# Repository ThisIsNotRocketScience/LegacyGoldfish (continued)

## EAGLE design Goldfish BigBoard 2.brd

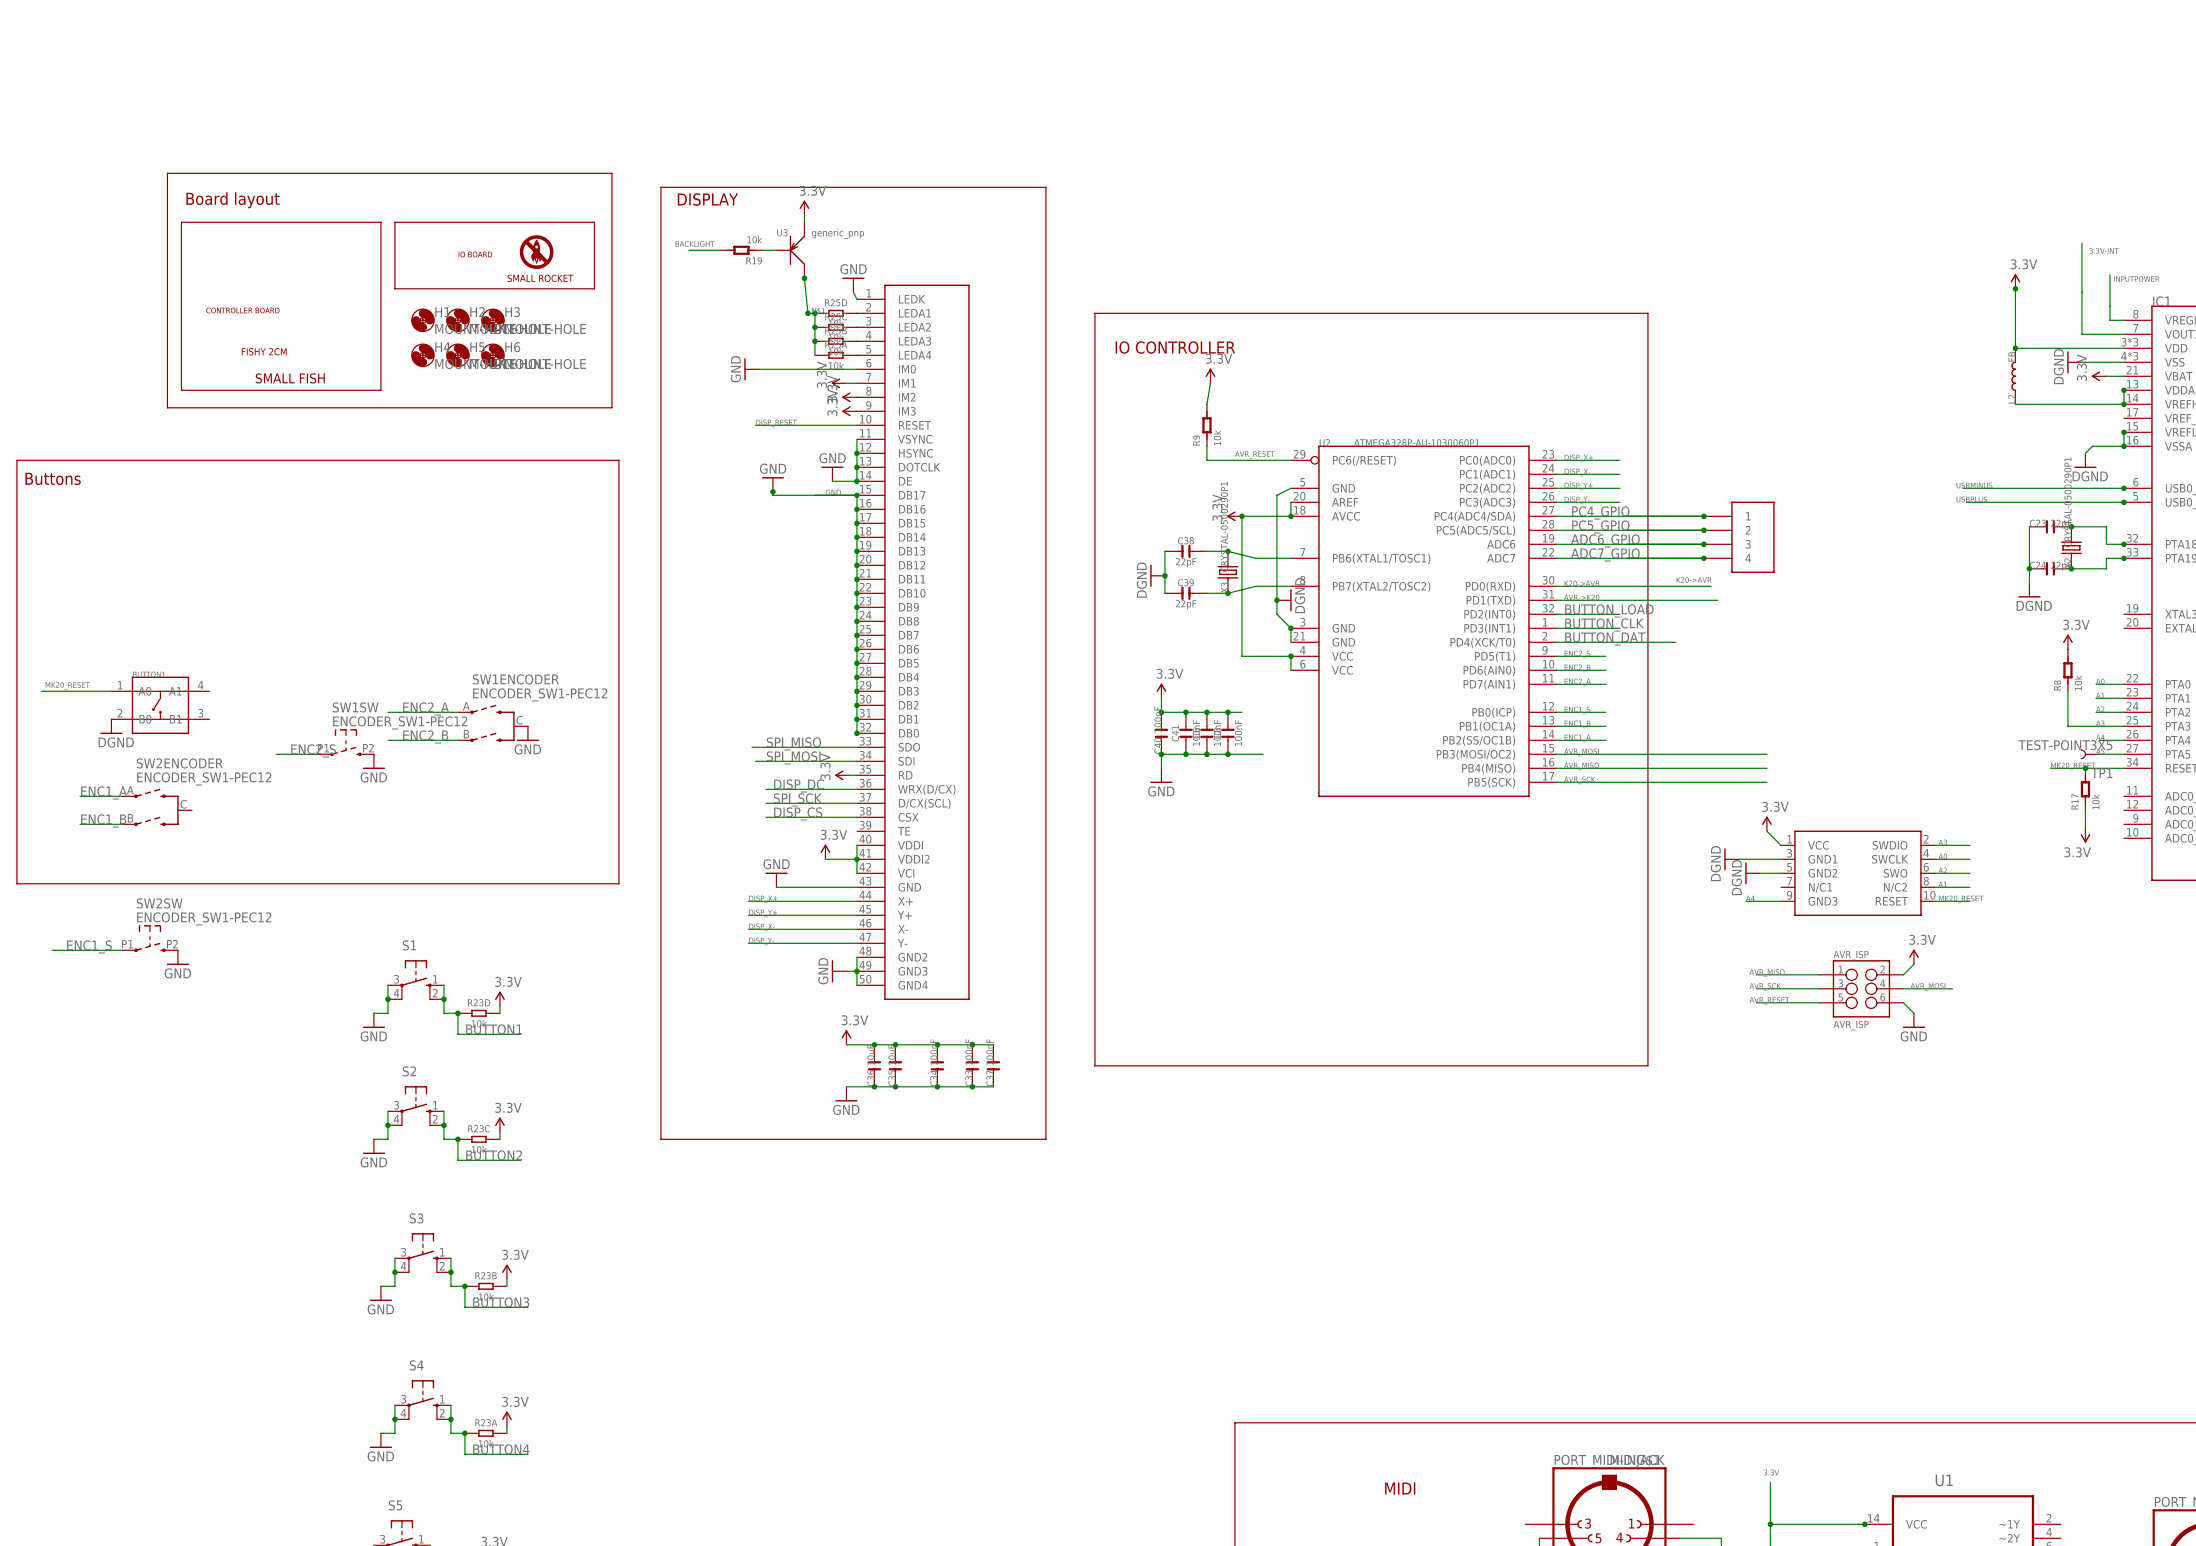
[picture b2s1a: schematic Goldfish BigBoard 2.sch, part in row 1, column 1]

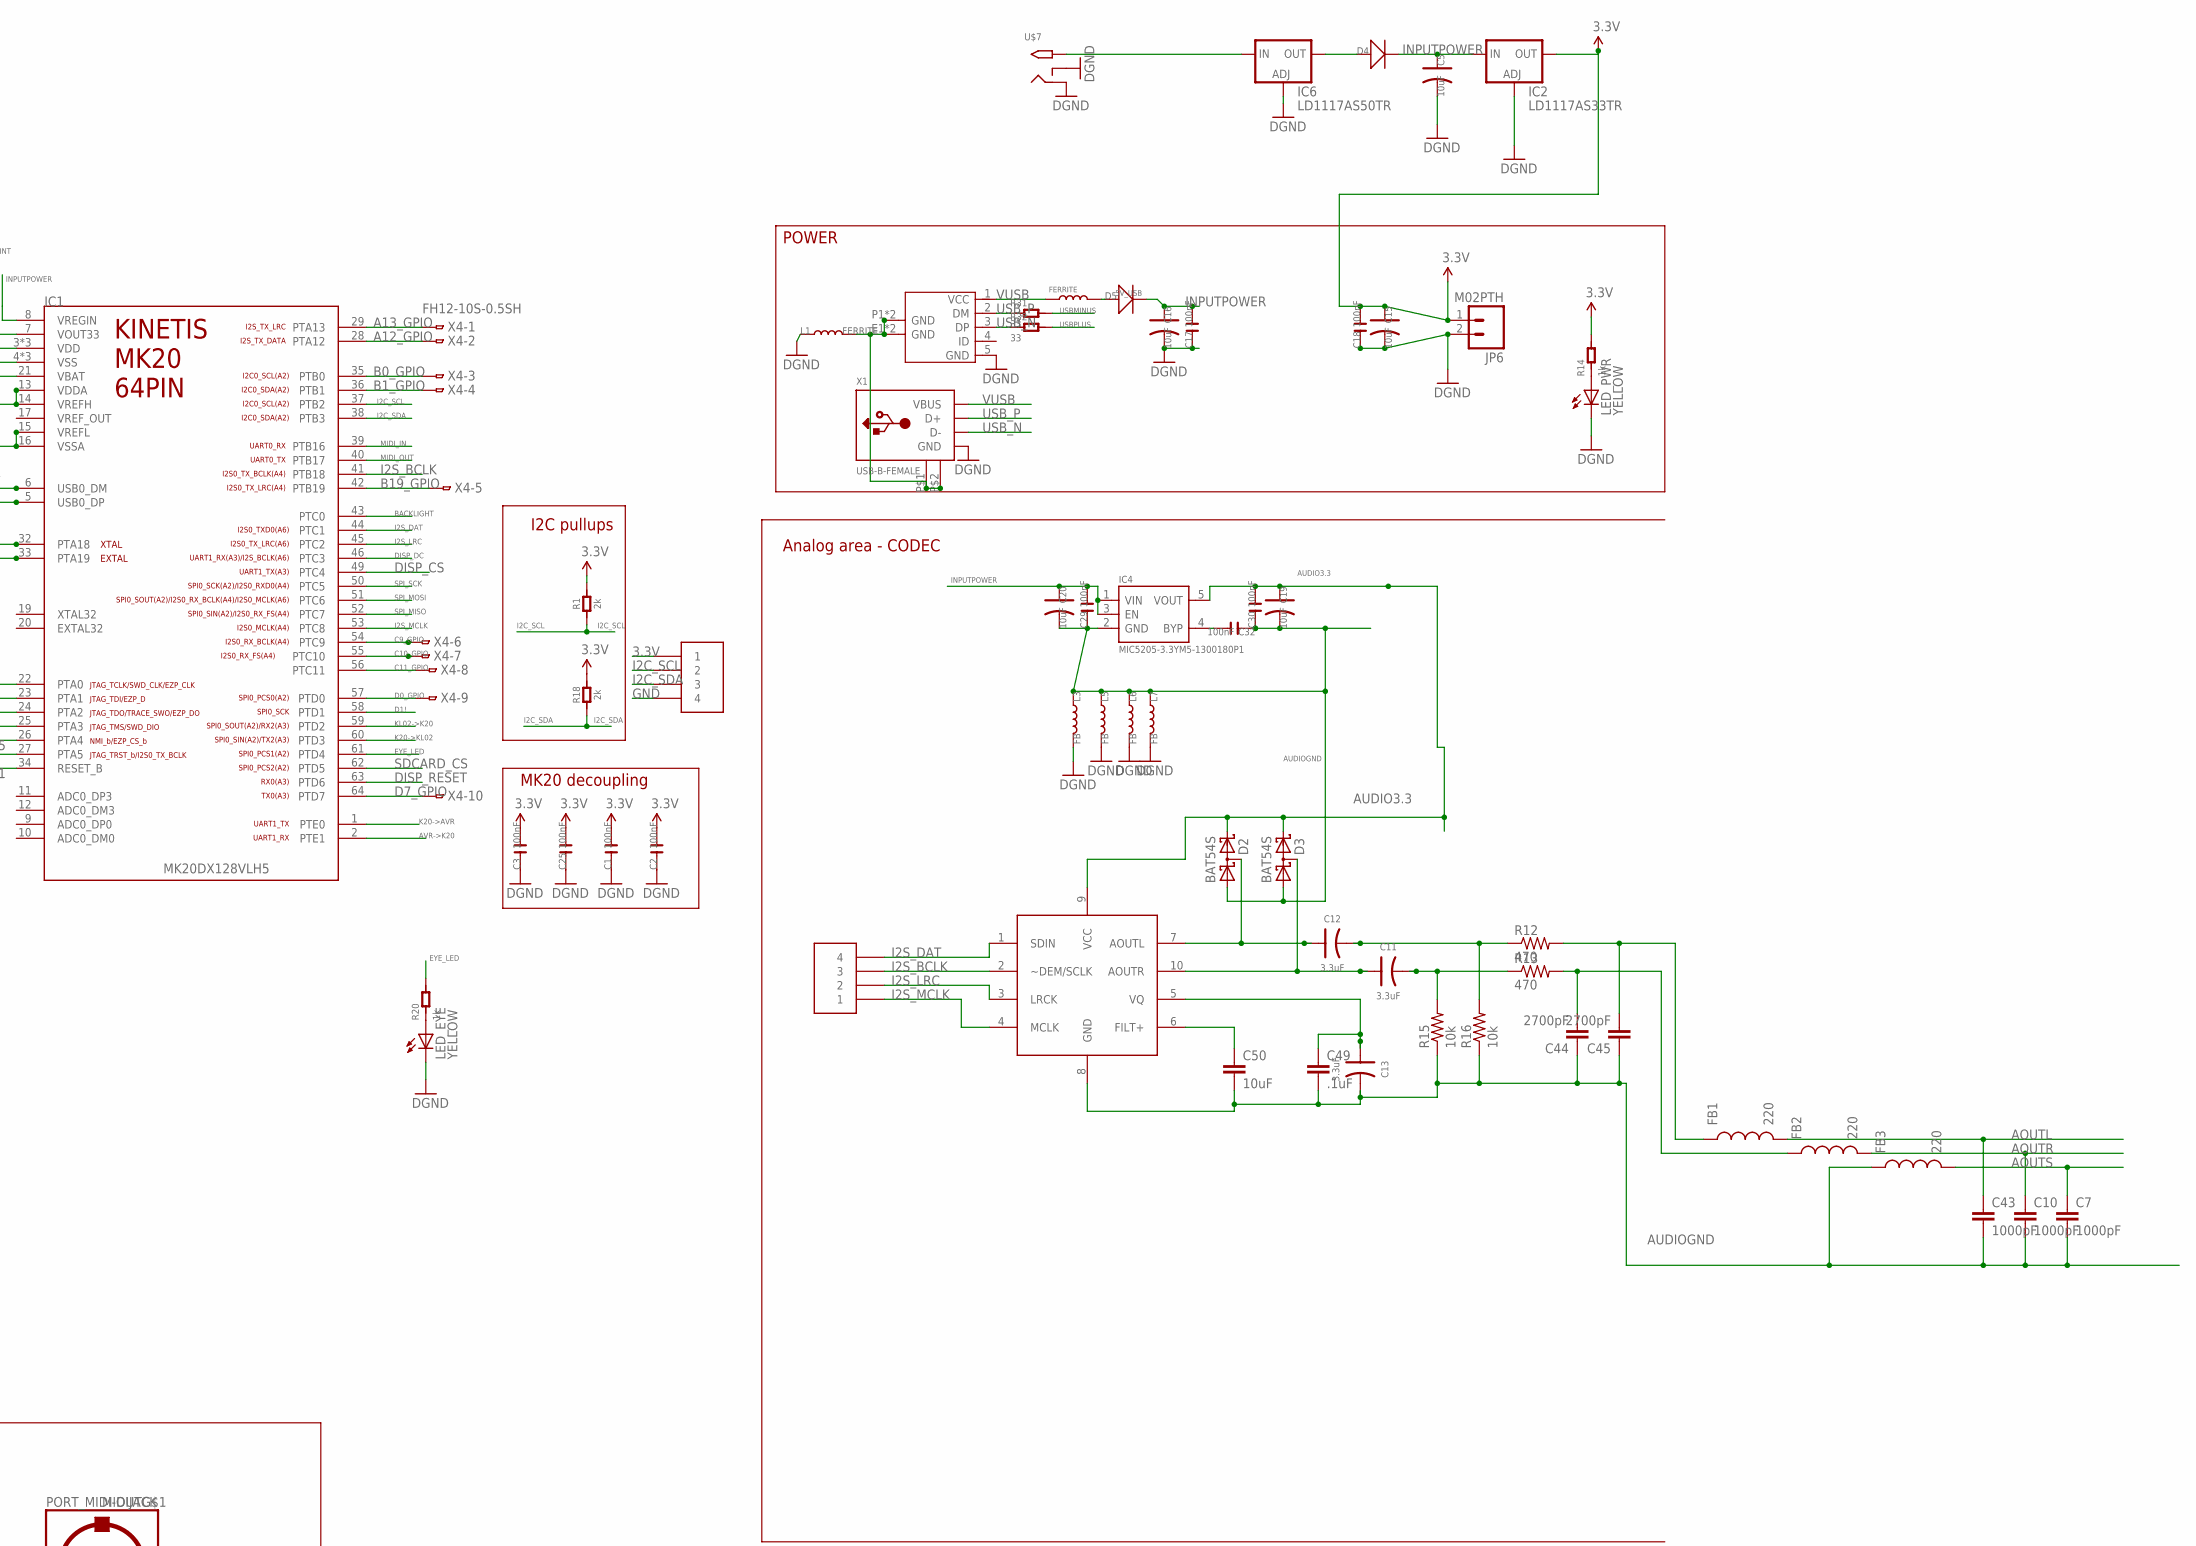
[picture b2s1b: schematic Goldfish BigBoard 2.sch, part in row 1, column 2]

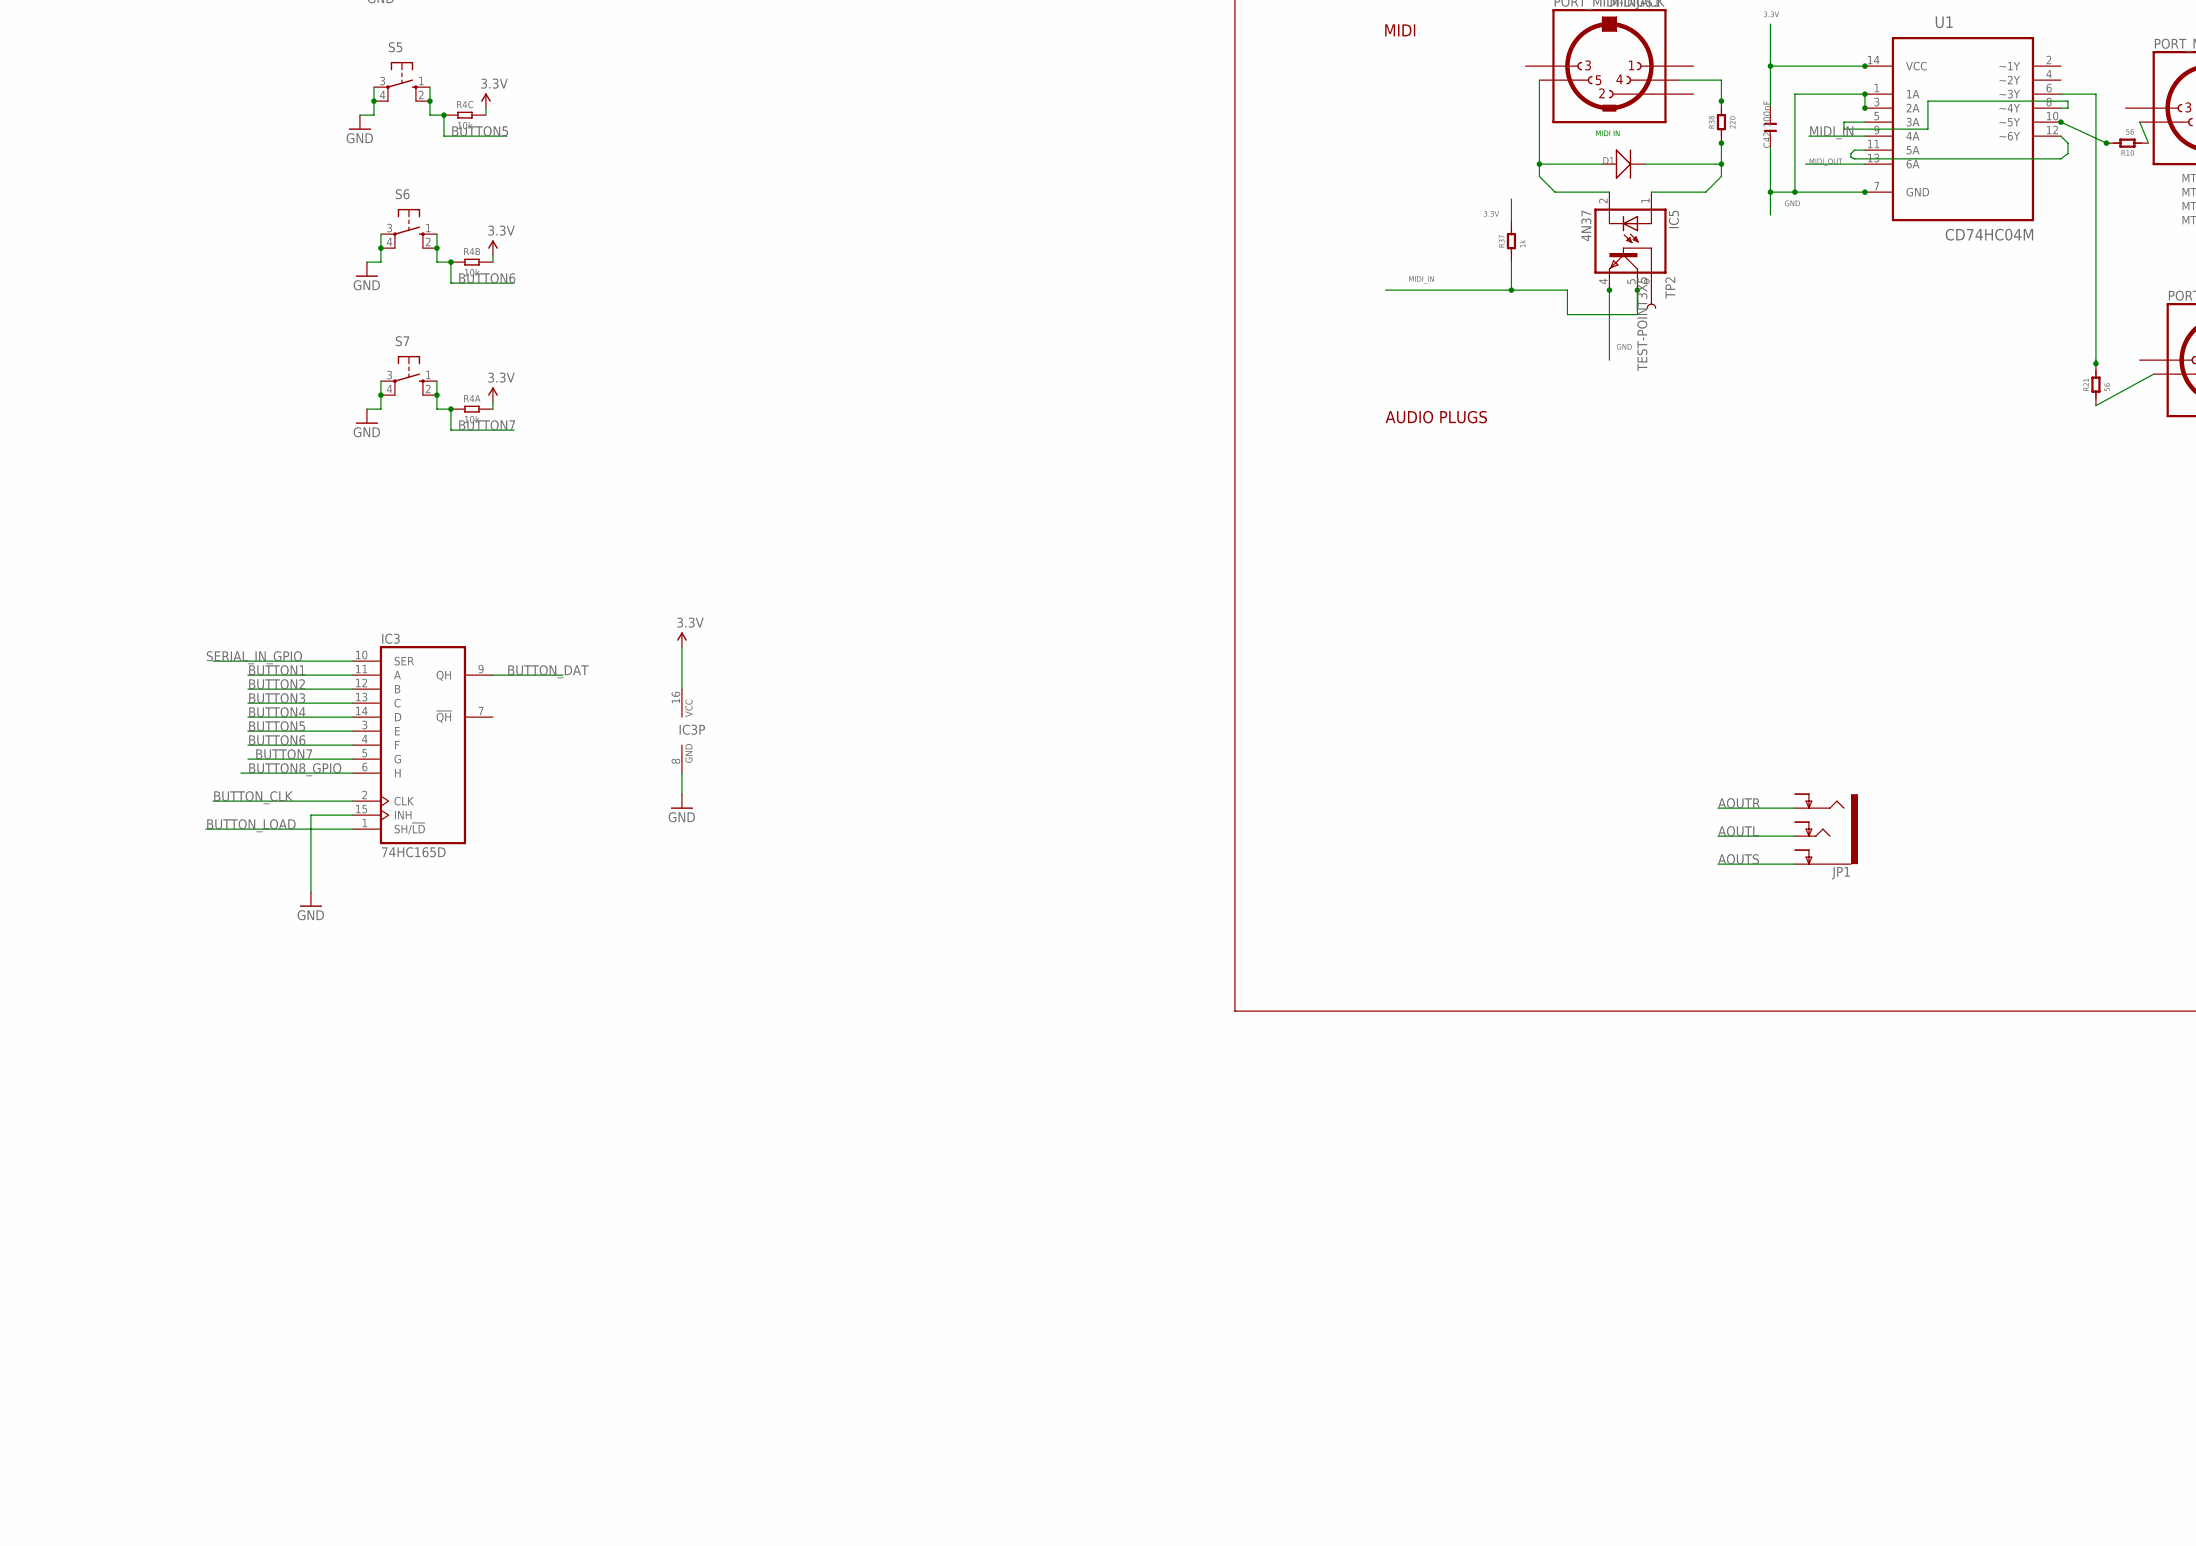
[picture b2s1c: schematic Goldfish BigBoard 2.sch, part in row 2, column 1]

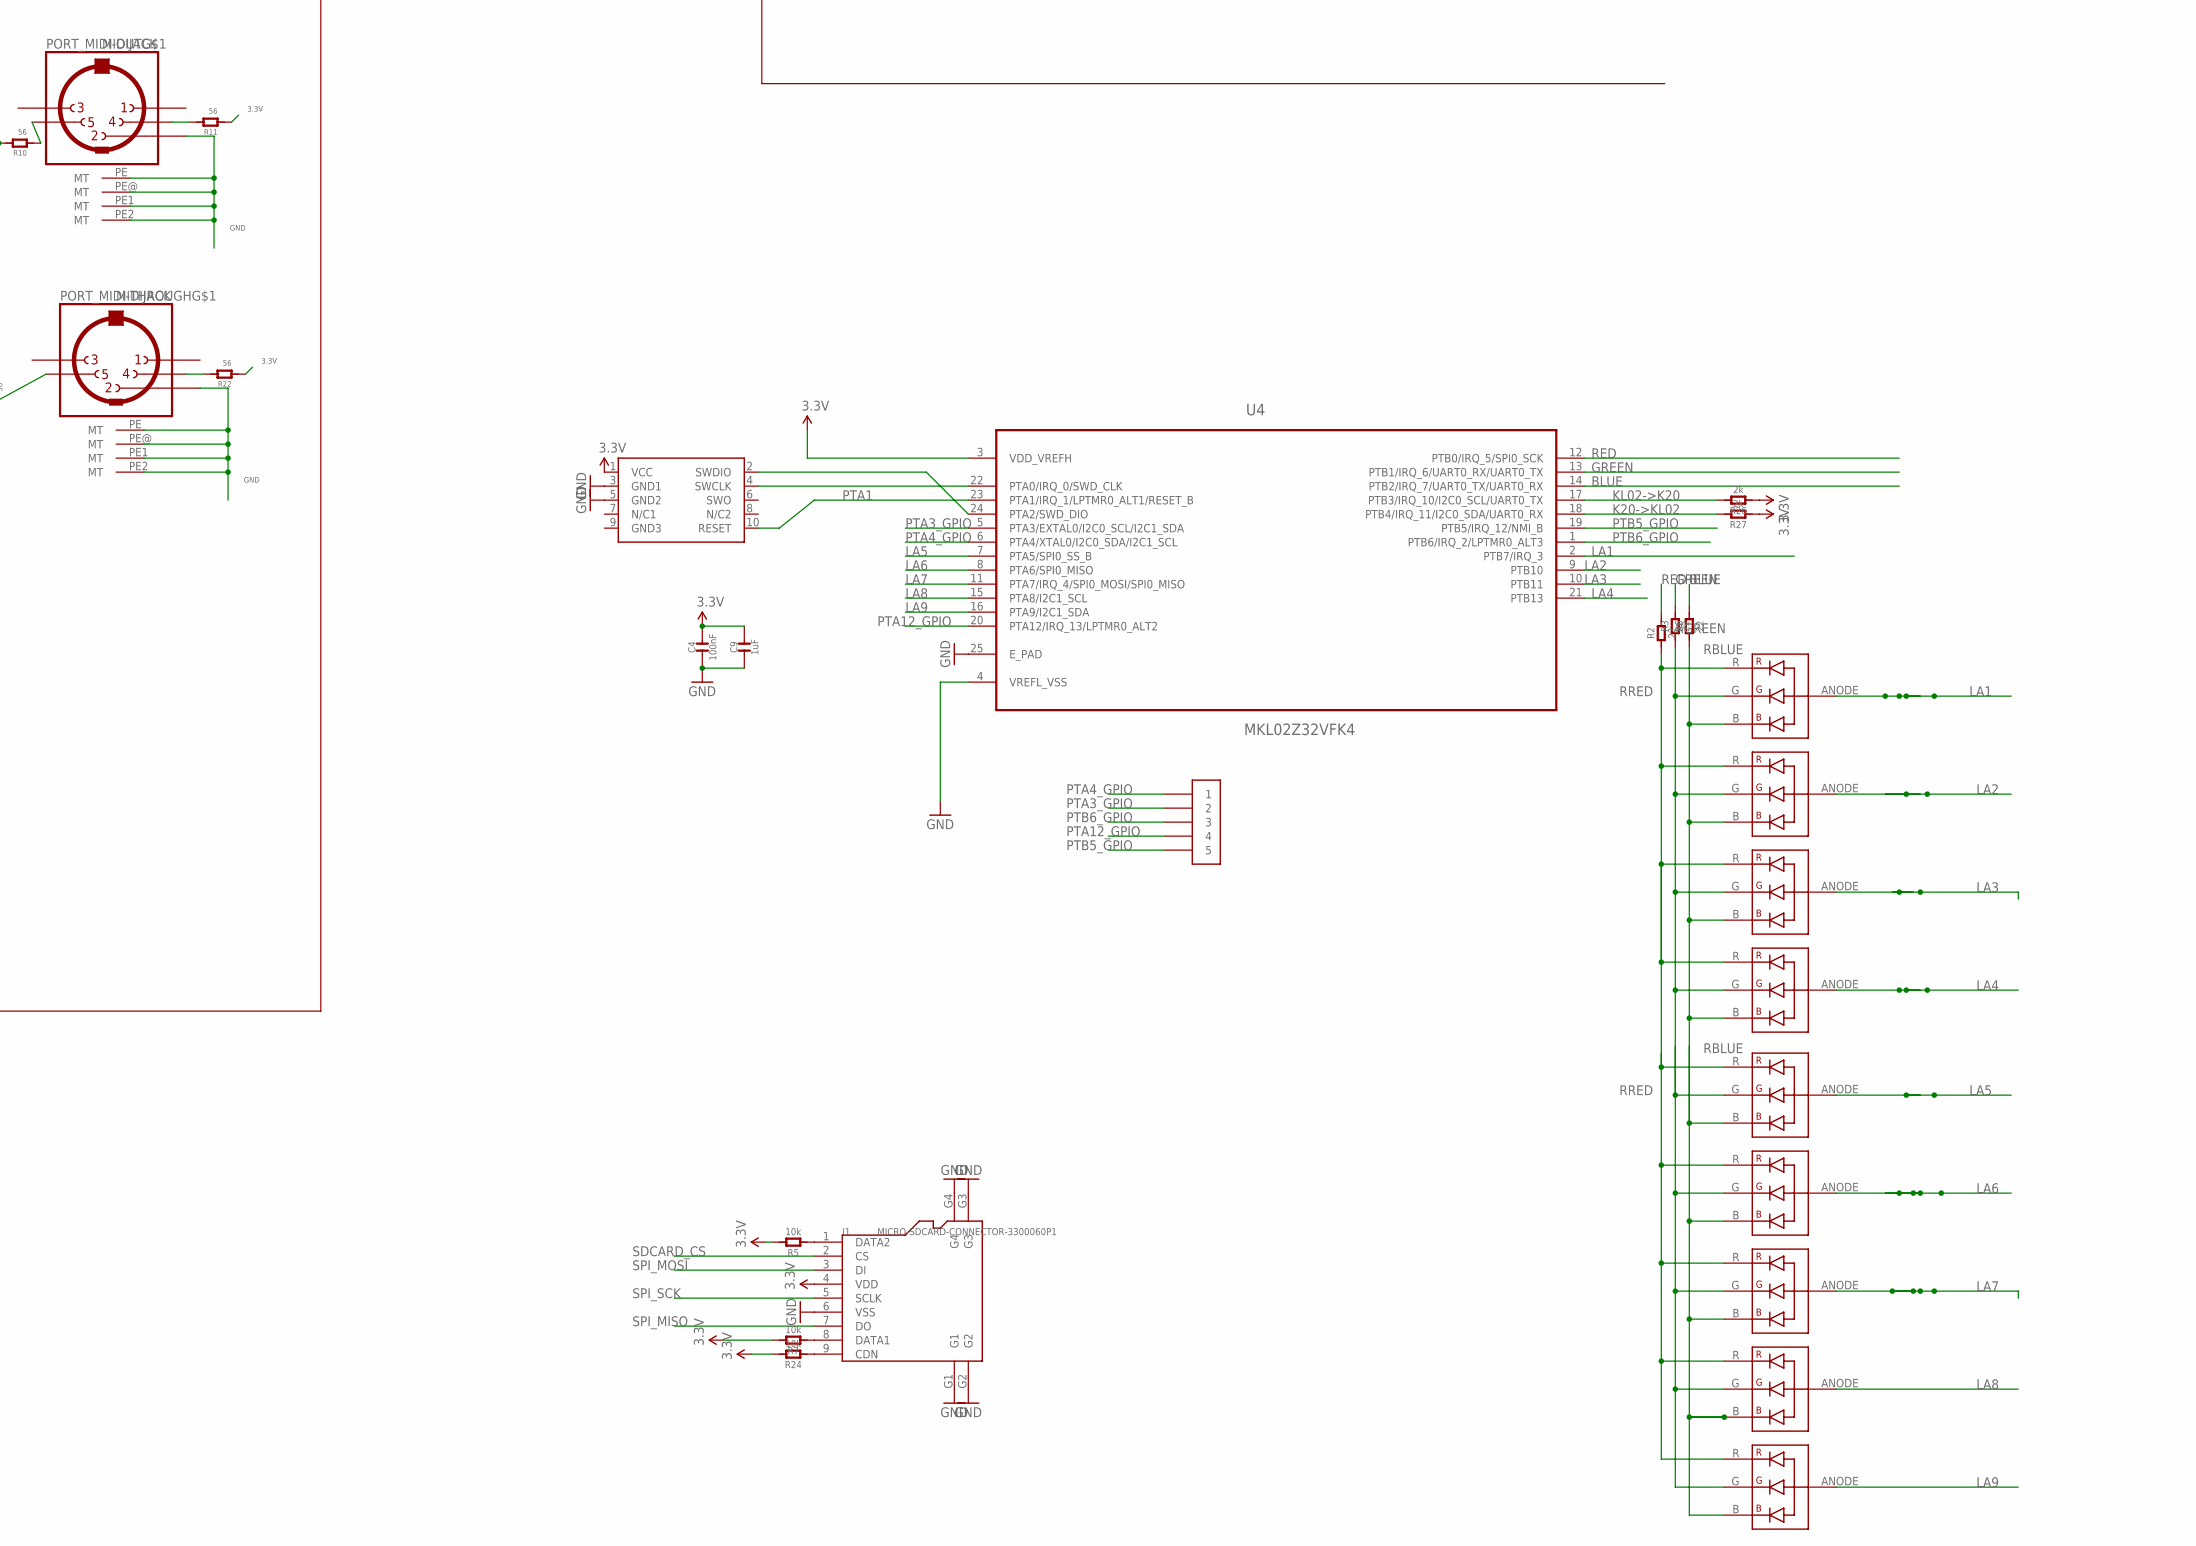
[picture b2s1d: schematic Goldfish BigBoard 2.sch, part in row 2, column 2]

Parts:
AVR_ISP: AVR_ISP; 2X3_SMT_POSTS
BUTTON1: BUTTON-4P-3100010P1; 4P-SMD-6.0X6.0X5.0H
C1, C2, C3, C4, C6, C8, C17, C18, C25, C29, C30, C32, C33, C34, C40, C41, C42: 100nF; C0603
C5, C15, C16, C19, C20: 10uF; AVX-A
C7, C10, C43: 1000pF; 0402-CAP
C9: 1uF; C0603
C11, C12, C13: 3.3uF; AVX-A
C23, C24, C38, C39: 22pF; C0603
C35: 10uF; C0603
C36: 10uF; C0805
C37: 100nF; C0805
C44, C45: 2700pF; 0402-CAP
C49: .1uF; 0402-CAP
C50: 10uF; 0402-CAP
D1, D4, D5: D-D1206; LL-34
D2, D3: BAT54S; SOT23
FB1, FB2, FB3: 220; 0805
H1, H2, H3, H4, H5, H6: MOUNT-HOLE; 3.2-NOMARKINGS-SMALLSAFEZONE
IC1: MK20DX128VLH5
IC2: LD1117AS33TR; SOT223
IC3: 74HC165D; SO16
IC4: MIC5205-3.3YM5-1300180P1; SOT23-5
IC5: 4N37; DIL06
IC6: LD1117AS50TR; SOT223
J1: MICRO-SDCARD-CONNECTOR-3300060P1; 9P-SMD-W-RING
J2: MICRO-USB-5P-340015001; B-SMD-5P
JP1: AUDIO-JACK4-.25-HORIZ-TRS; AUDIO-JACK-.25-INCH-HORIZ-PTH
JP6: M02PTH; 1X02
L1, L4: FERRITE; L0603
L2, L3, L5, L6, L7: FB; L0603
LED_EYE: YELLOW; CHIP-LED0603
LED_PWR: YELLOW; CHIP-LED0603
PORT_MIDI-IN: MIDIJACK; CP-2350
PORT_MIDI-OUT: MIDIJACK; CP-2350
PORT_MIDI-THROUGH: MIDIJACK; CP-2350
R1, R18, R26, R27: 2k; R0603
R2, R3, R6: 22; R0603
R4, R23, R25: 10k; R1206-8
R5, R7, R8, R9, R17, R19, R24: 10k; R0603
R10, R11, R21, R22: 56; R0603
R12, R13: 470; 0603-RES
R14, R20, R37: 1k; R0603
R15, R16: 10k; 0603-RES
R31, R32: 33; R0603
R38: 220; R0603
S1, S2, S3, S4, S5, S6, S7: 40-XX-ROUND; B3F-40XX-ROUND
SW1, SW2: ENCODER_SW1-PEC12; PEC12_INCREMENTAL_ENCODER
SWD1, SWD2: CORTEX_SWD; M50-3600542
TP1, TP2: TEST-POINT3X5; PAD.03X.05
U1: CD74HC04M; SOIC127P600X175-14N
U2: ATMEGA328P-AU-1030060P1; TQFP32
U3: generic_pnp; SOT23
U4: MKL02Z32VFK4; QFN50P400X400X100-25N
U$1: 2.8"TFT2.8"TFT; 2.8"TFT
U$3: FISH2CM_SILK; FISH_WITHSILK
U$4: FISH_SMALL
U$6: CS4344-DAC; TSSOP-10
U$7: 2.1MMJACKTHM; 163-179PH-EX
U$8: SMALLROCKET
U$9, U$10, U$12, U$13, U$14, U$15, U$16, U$17, U$18: RGBLED_COMMONANODE; 3.5X2.8_RGB_LED
U$11: M05
U$20, U$21, U$22: M04
X1: USB-B-FEMALE; FCI61729
X2, X3: CRYSTAL-0500290P1; 2P-SMD-5.0X3.2
X4: FH12-10S-0.5SH

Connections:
3.3V: AVR_ISP.2, C1.2, C2.2, C3.2, C4.2, C6.2, C8.2, C9.2, C15.+ (1), C18.2, C25.2, C33.2, C34.2, C35.2, C36.2, C37.2, C40.2, C41.2, C42.2, IC1.3 (VDD), IC1.21 (VBAT), IC1.30 (VDD), IC1.48 (VDD), IC2.2 (OUT), IC2.4 (OUT), IC3.16 (VCC), J1.4 (VDD), JP6.1, L2.2, R1.2, R4.6 (2), R4.7 (2), R4.8 (2), R5.2, R7.2, R8.2, R9.2, R11.1, R14.2, R17.1, R18.2, R22.1, R23.5 (2), R23.6 (2), R23.7 (2), R23.8 (2), R24.2, R26.1, R27.1, R37.2, SWD1.1 (VCC), SWD2.1 (VCC), U1.14 (VCC), U2.4 (VCC), U2.6 (VCC), U2.18 (AVCC), U2.20 (AREF), U3.2 (E), U4.3 (VDD_VREFH), U$1.7 (IM1), U$1.8 (IM2), U$1.9 (IM3), U$1.35 (RD), U$1.40 (VDDI), U$1.41 (VDDI2), U$1.42 (VCI), U$22.P$1 (1)
3.3V-INT: IC1.7 (VOUT33)
5V_DC: D4.A (+), IC6.2 (OUT), IC6.4 (OUT)
5V_USB: D5.A (+), L4.2
A0: IC1.22 (PTA0), SWD1.4 (SWCLK)
A1: IC1.23 (PTA1), SWD1.8 (N/C2)
A2: IC1.24 (PTA2), SWD1.6 (SWO)
A3: IC1.25 (PTA3), R8.1, SWD1.2 (SWDIO)
A4: IC1.26 (PTA4), SWD1.9 (GND3)
A5: IC1.27 (PTA5), TP1.P$1
A12_GPIO: IC1.28 (PTA12), X4.2
A13_GPIO: IC1.29 (PTA13), X4.1
ADC6_GPIO: U2.19 (ADC6), U$20.P$3 (3)
ADC7_GPIO: U2.22 (ADC7), U$20.P$4 (4)
AOUTL: C43.1, FB1.2, JP1.P$6 (TIP)
AOUTL_C: C12.+ (1), D2.3 (C1A2), U$6.7 (AOUTL)
AOUTL_FB: C45.2, FB1.1, R12.2
AOUTL_R: C12.- (2), R12.1, R16.2
AOUTR: C10.1, FB2.2, JP1.P$4 (RING)
AOUTR_C: C11.+ (1), D3.3 (C1A2), U$6.10 (AOUTR)
AOUTR_FB: C44.2, FB2.1, R13.2
AOUTR_R: C11.- (2), R13.1, R15.2
AOUTS: C7.1, FB3.2, JP1.P$2 (EARTH)
AUDIO3.3: C19.+ (1), C30.2, D2.2 (C2), D3.2 (C2), IC4.5 (VOUT), U$6.9 (VCC)
AUDIOGND: C7.2, C10.2, C13.- (2), C19.- (2), C20.- (2), C29.1, C30.1, C32.1, C43.2, C44.1, C45.1, C49.2, C50.2, D2.1 (A1), D3.1 (A1), FB3.1, IC4.2 (GND), L3.1, L5.1, L6.1, L7.1, R15.1, R16.1, U$6.8 (GND)
AVR->K20: IC1.2 (PTE1), U2.31 (PD1(TXD))
AVR_MISO: AVR_ISP.1, U2.16 (PB4(MISO))
AVR_MOSI: AVR_ISP.4, U2.15 (PB3(MOSI/OC2))
AVR_RESET: AVR_ISP.5, R9.1, U2.29 (PC6(/RESET))
AVR_SCK: AVR_ISP.3, U2.17 (PB5(SCK))
B0_GPIO: IC1.35 (PTB0), X4.3
B1_GPIO: IC1.36 (PTB1), X4.4
B19_GPIO: IC1.42 (PTB19), X4.5
BACKLIGHT: IC1.43 (PTC0), R19.2
BLUE: R6.2, U4.14 (PTB2/IRQ_7/UART0_TX/UART0_RX)
BUTTON1: IC3.11 (A), R23.4 (1), S1.1 (S), S1.2 (S1)
BUTTON2: IC3.12 (B), R23.3 (1), S2.1 (S), S2.2 (S1)
BUTTON3: IC3.13 (C), R23.2 (1), S3.1 (S), S3.2 (S1)
BUTTON4: IC3.14 (D), R23.1, S4.1 (S), S4.2 (S1)
BUTTON5: IC3.3 (E), R4.3 (1), S5.1 (S), S5.2 (S1)
BUTTON6: IC3.4 (F), R4.2 (1), S6.1 (S), S6.2 (S1)
BUTTON7: IC3.5 (G), R4.1, S7.1 (S), S7.2 (S1)
BUTTON8_GPIO: IC3.6 (H)
BUTTON_CLK: IC3.2 (CLK), U2.1 (PD3(INT1))
BUTTON_DAT: IC3.9 (QH), U2.2 (PD4(XCK/T0))
BUTTON_LOAD: IC3.1 (SH/!LD), U2.32 (PD2(INT0))
C9_GPIO: IC1.54 (PTC9), X4.6
C10_GPIO: IC1.55 (PTC10), X4.7
C11_GPIO: IC1.56 (PTC11), X4.8
D0_GPIO: IC1.57 (PTD0), X4.9
D1!: IC1.58 (PTD1)
D7_GPIO: IC1.64 (PTD7), X4.10
DISP_CS: IC1.49 (PTC4), U$1.38 (CSX)
DISP_DC: IC1.46 (PTC3), U$1.36 (WRX(D/CX))
DISP_RESET: IC1.63 (PTD6), U$1.10 (RESET)
DISP_X+: U2.23 (PC0(ADC0)), U$1.44 (X+)
DISP_X-: U2.24 (PC1(ADC1)), U$1.46 (X-)
DISP_Y+: U2.25 (PC2(ADC2)), U$1.45 (Y+)
DISP_Y-: U2.26 (PC3(ADC3)), U$1.47 (Y-)
ENC1_A: SW2.A, U2.14 (PB2(SS/OC1B))
ENC1_B: SW2.B, U2.13 (PB1(OC1A))
ENC1_S: SW2.P1 (1), U2.12 (PB0(ICP))
ENC2_A: SW1.A, U2.11 (PD7(AIN1))
ENC2_B: SW1.B, U2.10 (PD6(AIN0))
ENC2_S: SW1.P1 (1), U2.9 (PD5(T1))
EYE_LED: IC1.61 (PTD4), R20.2
FILT+: C50.1, U$6.6 (FILT+)
GND: AVR_ISP.6, BUTTON1.2 (B0), C1.1, C2.1, C3.1, C4.1, C5.- (2), C6.1, C8.1, C9.1, C15.- (2), C16.- (2), C17.1, C18.1, C23.1, C24.1, C25.1, C33.1, C34.1, C35.1, C36.1, C37.1, C38.1, C39.1, C40.1, C41.1, C42.1, IC1.4 (VSS), IC1.15 (VREFL), IC1.16 (VSSA), IC1.31 (VSS), IC1.47 (VSS), IC2.1 (ADJ), IC3.8 (GND), IC3.15 (INH), IC5.4 (EMI), IC6.1 (ADJ), J1.6 (VSS), J1.G1, J1.G2, J1.G3, J1.G4, J2.5 (GND), JP6.2, L1.1, L3.2, L5.2, L6.2, L7.2, LED_EYE.C, LED_PWR.C, PORT_MIDI-OUT.2, PORT_MIDI-OUT.PE (MT), PORT_MIDI-OUT.PE1 (MT), PORT_MIDI-OUT.PE2 (MT), PORT_MIDI-OUT.PE@ (MT), PORT_MIDI-THROUGH.2, PORT_MIDI-THROUGH.PE (MT), PORT_MIDI-THROUGH.PE1 (MT), PORT_MIDI-THROUGH.PE2 (MT), PORT_MIDI-THROUGH.PE@ (MT), S1.3, S1.4 (P1), S2.3, S2.4 (P1), S3.3, S3.4 (P1), S4.3, S4.4 (P1), S5.3, S5.4 (P1), S6.3, S6.4 (P1), S7.3, S7.4 (P1), SW1.C, SW1.P2 (2), SW2.P2 (2), SWD1.3 (GND1), SWD1.5 (GND2), SWD2.3 (GND1), SWD2.5 (GND2), U1.1 (1A), U1.3 (2A), U1.7 (GND), U2.3 (GND), U2.5 (GND), U2.21 (GND), U4.4 (VREFL_VSS), U4.25 (E_PAD), U$1.1 (LEDK), U$1.6 (IM0), U$1.11 (VSYNC), U$1.12 (HSYNC), U$1.13 (DOTCLK), U$1.14 (DE), U$1.15 (DB17), U$1.16 (DB16), U$1.17 (DB15), U$1.18 (DB14), U$1.19 (DB13), U$1.20 (DB12), U$1.21 (DB11), U$1.22 (DB10), U$1.23 (DB9), U$1.24 (DB8), U$1.25 (DB7), U$1.26 (DB6), U$1.27 (DB5), U$1.28 (DB4), U$1.29 (DB3), U$1.30 (DB2), U$1.31 (DB1), U$1.32 (DB0), U$1.43 (GND), U$1.48 (GND2), U$1.49 (GND3), U$1.50 (GND4), U$7.RING, U$7.RING_SW, U$22.P$4 (4), X1.4 (GND)
GREEN: R3.2, U4.13 (PTB1/IRQ_6/UART0_RX/UART0_TX)
I2C_SCL: IC1.37 (PTB2), R1.1, U$22.P$2 (2)
I2C_SDA: IC1.38 (PTB3), R18.1, U$22.P$3 (3)
I2S_BCLK: IC1.41 (PTB18), U$6.2 (~DEM/SCLK), U$21.P$3 (3)
I2S_DAT: IC1.44 (PTC1), U$6.1 (SDIN), U$21.P$4 (4)
I2S_LRC: IC1.45 (PTC2), U$6.3 (LRCK), U$21.P$2 (2)
I2S_MCLK: IC1.53 (PTC8), U$6.4 (MCLK), U$21.P$1 (1)
IC1: U1.11 (5A), U1.12 (~6Y)
INPUTPOWER: C5.+ (1), C16.+ (1), C17.2, C20.+ (1), C29.2, D4.C (-), D5.C (-), IC1.8 (VREGIN), IC2.3 (IN), IC4.1 (VIN), IC4.3 (EN)
K20->AVR: IC1.1 (PTE0), U2.30 (PD0(RXD))
K20->KL02: IC1.60 (PTD3), R27.2, U4.18 (PTB4/IRQ_11/I2C0_SDA/UART0_RX)
KL02->K20: IC1.59 (PTD2), R26.2, U4.17 (PTB3/IRQ_10/I2C0_SCL/UART0_TX)
LA1: U4.2 (PTB7/IRQ_3), U$9.ANODE
LA2: U4.9 (PTB10), U$10.ANODE
LA3: U4.10 (PTB11), U$12.ANODE
LA4: U4.21 (PTB13), U$13.ANODE
LA5: U4.7 (PTA5/SPI0_SS_B), U$14.ANODE
LA6: U4.8 (PTA6/SPI0_MISO), U$15.ANODE
LA7: U4.11 (PTA7/IRQ_4/SPI0_MOSI/SPI0_MISO), U$16.ANODE
LA8: U4.15 (PTA8/I2C1_SCL), U$17.ANODE
LA9: U4.16 (PTA9/I2C1_SDA), U$18.ANODE
MIDI_IN: IC1.39 (PTB16), IC5.5 (COL), R37.1, U1.9 (4A)
MIDI_OUT: IC1.40 (PTB17), U1.13 (6A)
MK20_RESET: BUTTON1.1 (A0), IC1.34 (RESET_B), R17.2, SWD1.10 (RESET)
unnamed: R25.1, R25.2 (1), R25.3 (1), R25.4 (1), U3.3 (C)
unnamed: LED_PWR.A, R14.1
unnamed: J2.E1 (GND), J2.E2 (GND), J2.P1 (GND), J2.P2 (GND), L1.2, X1.P$1 (GND1), X1.P$2 (GND2)
unnamed: R10.2, U1.10 (~5Y)
unnamed: R25.5 (2), U$1.2 (LEDA1)
unnamed: PORT_MIDI-THROUGH.5, R21.1
unnamed: IC6.3 (IN), U$7.TIP
unnamed: SWD2.4 (SWCLK), U4.22 (PTA0/IRQ_0/SWD_CLK)
unnamed: C23.2, IC1.32 (PTA18), X2.2
unnamed: C24.2, IC1.33 (PTA19), X2.1
unnamed: R19.1, U3.1 (B)
unnamed: SWD2.2 (SWDIO), U4.24 (PTA2/SWD_DIO)
unnamed: C32.2, IC4.4 (BYP)
unnamed: J1.1 (DATA2), R5.1
unnamed: IC5.6 (BAS), TP2.P$1
unnamed: R25.6 (2), U$1.3 (LEDA2)
unnamed: LED_EYE.A, R20.1
unnamed: J1.8 (DATA1), R7.1
unnamed: J1.9 (CDN), R24.1
unnamed: PORT_MIDI-THROUGH.4, R22.2
unnamed: R25.7 (2), U$1.4 (LEDA3)
unnamed: R25.8 (2), U$1.5 (LEDA4)
unnamed: PORT_MIDI-OUT.5, R10.1
unnamed: PORT_MIDI-OUT.4, R11.2
unnamed: IC1.13 (VDDA), IC1.14 (VREFH), L2.1
unnamed: C38.2, U2.7 (PB6(XTAL1/TOSC1)), X3.2
unnamed: C39.2, U2.8 (PB7(XTAL2/TOSC2)), X3.1
unnamed: R21.2, U1.6 (~3Y)
unnamed: U1.5 (3A), U1.8 (~4Y)
unnamed: D1.A (+), IC5.2 (C), PORT_MIDI-IN.5
unnamed: D1.C (-), IC5.1 (A), R38.1
unnamed: PORT_MIDI-IN.4, R38.2
PC4_GPIO: U2.27 (PC4(ADC4/SDA)), U$20.P$1 (1)
PC5_GPIO: U2.28 (PC5(ADC5/SCL)), U$20.P$2 (2)
PTA1: SWD2.10 (RESET), U4.23 (PTA1/IRQ_1/LPTMR0_ALT1/RESET_B)
PTA3_GPIO: U4.5 (PTA3/EXTAL0/I2C0_SCL/I2C1_SDA), U$11.P$2 (2)
PTA4_GPIO: U4.6 (PTA4/XTAL0/I2C0_SDA/I2C1_SCL), U$11.P$1 (1)
PTA12_GPIO: U4.20 (PTA12/IRQ_13/LPTMR0_ALT2), U$11.P$4 (4)
PTB5_GPIO: U4.19 (PTB5/IRQ_12/NMI_B), U$11.P$5 (5)
PTB6_GPIO: U4.1 (PTB6/IRQ_2/LPTMR0_ALT3), U$11.P$3 (3)
RBLUE: R6.1, U$9.B, U$10.B, U$12.B, U$13.B, U$14.B, U$15.B, U$16.B, U$17.B, U$18.B
RED: R2.2, U4.12 (PTB0/IRQ_5/SPI0_SCK)
RGREEN: R3.1, U$9.G, U$10.G, U$12.G, U$13.G, U$14.G, U$15.G, U$16.G, U$17.G, U$18.G
RRED: R2.1, U$9.R, U$10.R, U$12.R, U$13.R, U$14.R, U$15.R, U$16.R, U$17.R, U$18.R
SDCARD_CS: IC1.62 (PTD5), J1.2 (CS)
SERIAL_IN_GPIO: IC3.10 (SER)
SPI_MISO: IC1.52 (PTC7), J1.7 (DO), U$1.33 (SDO)
SPI_MOSI: IC1.51 (PTC6), J1.3 (DI), U$1.34 (SDI)
SPI_SCK: IC1.50 (PTC5), J1.5 (SCLK), U$1.37 (D/CX(SCL))
USBMINUS: IC1.6 (USB0_DM), R31.2
USBPLUS: IC1.5 (USB0_DP), R32.2
USB_N: J2.3 (DP), R32.1, X1.2 (D-)
USB_P: J2.2 (DM), R31.1, X1.3 (D+)
VQ: C13.+ (1), C49.1, U$6.5 (VQ)
VUSB: J2.1 (VCC), L4.1, X1.1 (VBUS)

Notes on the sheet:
DISPLAY
IO CONTROLLER
POWER
IO BOARD
CONTROLLER BOARD
I2C pullups
MK20 decoupling
Board layout
Buttons
Analog area - CODEC
MIDI IN
MIDI
AUDIO PLUGS

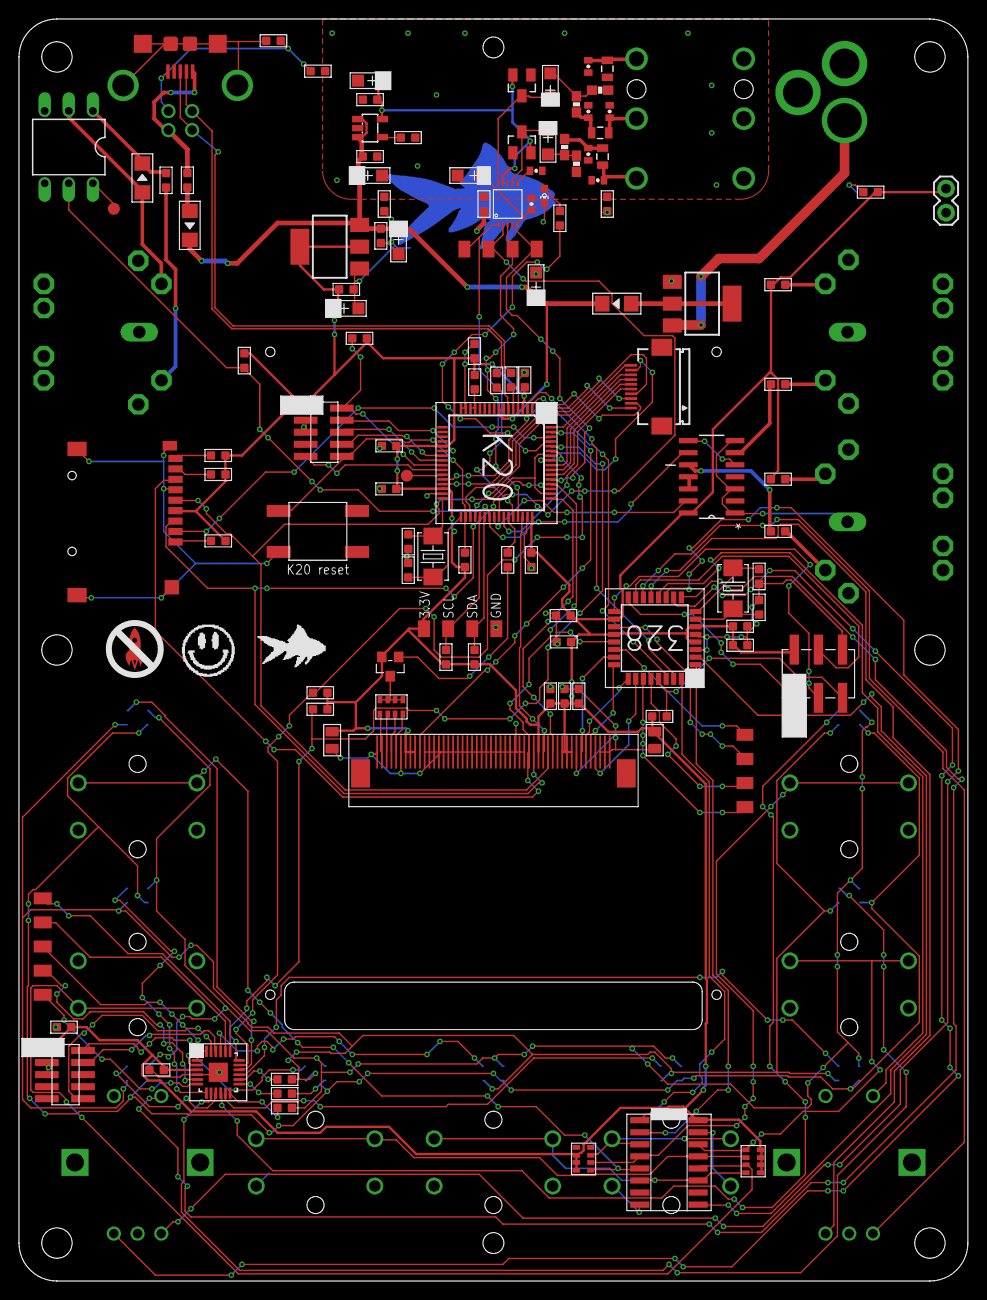
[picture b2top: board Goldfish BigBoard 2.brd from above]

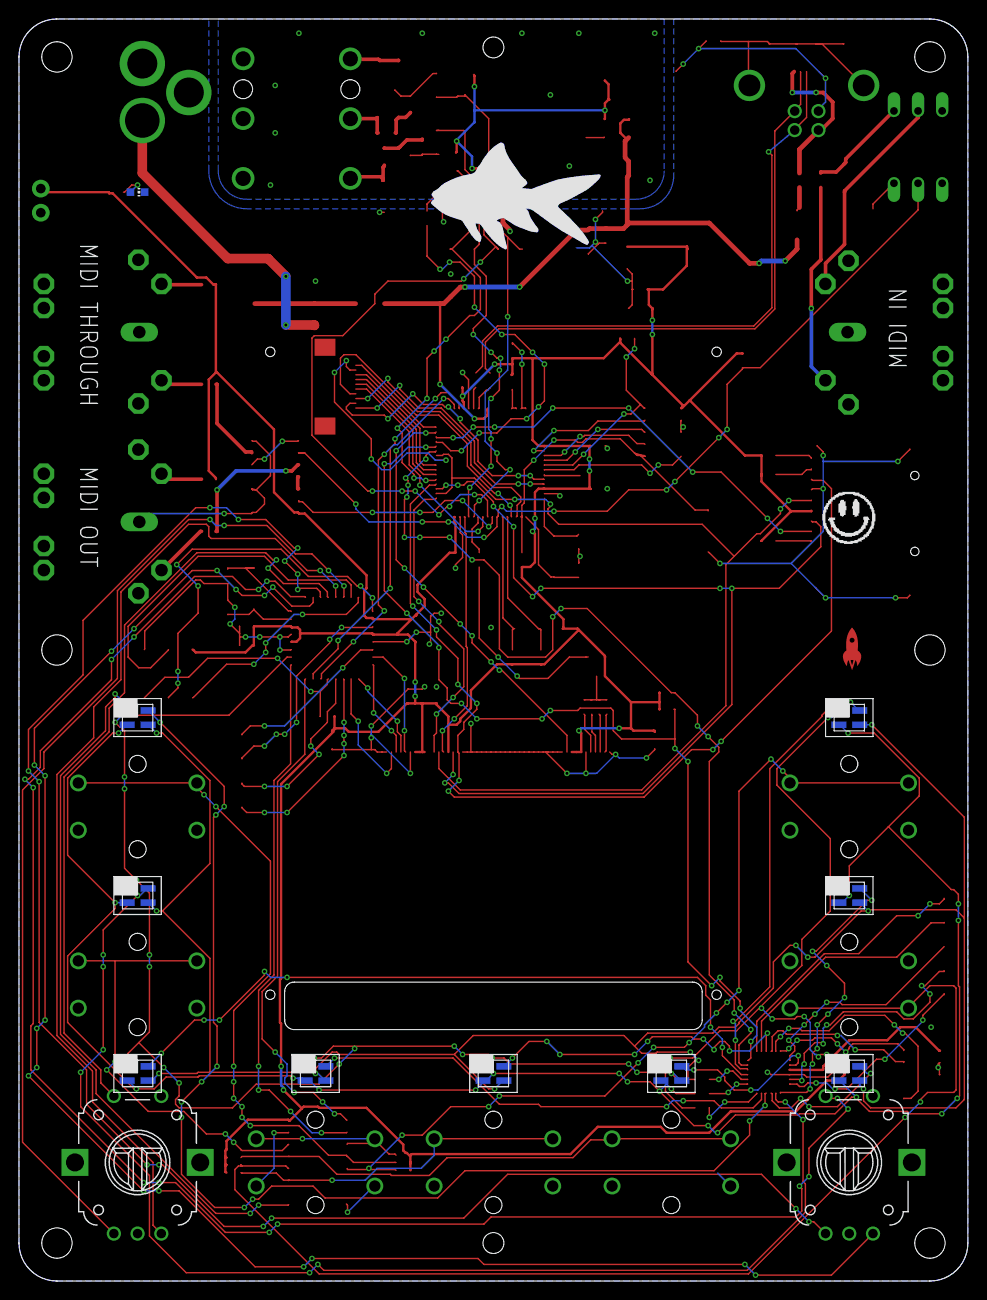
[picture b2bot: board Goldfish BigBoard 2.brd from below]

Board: 2 copper layers, 100.0 x 133.0 mm, 153 parts (21 on the bottom side), 143 nets.

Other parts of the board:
U$2, U$5: 2.2-NOMARKINGS-SMALLSAFEZONE
U$19, U$23: ACIDSMILE

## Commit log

2015-11-25 Some boards for earlier revisions
